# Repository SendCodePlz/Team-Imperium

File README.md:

<div align="center">

# Team Imperium — Battery Management System

**A hardware + software BMS for 3-series Li-ion packs: real-time fault detection, graded protection, and SOC/SOH estimation**

*Caterpillar Tech Challenge · IIT Madras*

</div>

---

## Overview

Team Imperium's BMS watches a battery pack's sensors in real time, works out whether something
dangerous is happening, and disconnects the pack before it fails. It has two parts:

- **Custom PCB.** A 2-layer board built around a TI **BQ77915** cell protector, with
  back-to-back **CSD17570Q5B** charge/discharge MOSFETs, an **INA226** current/power monitor on
  a 2 mΩ shunt, three thermistor inputs, and a socket for an **ESP32** dev board.
- **Firmware and toolchain.** ESP32 firmware on FreeRTOS that runs **14 physics-based fault
  detectors**, a severity → action-tier → contactor chain, and an **Unscented Kalman Filter**
  for State of Charge and State of Health. A Python toolchain replays labelled data through
  the same algorithm (Software-in-the-Loop) and scores it against ground truth.

### Highlights

| | |
|---|---|
| **Fault detection** | 14 detectors covering thermal, gas/pressure, mechanical impact, sensor loss, micro-short, voltage/thermal gradients, over/under-voltage, over-current and thermal-runaway precursors |
| **Graded response** | Each fault gets a 0–1 severity, which maps to one of 4 tiers: `NORMAL → INHIBIT_CHG → OPEN_ALL → LATCH_OPEN` |
| **State estimation** | Joint SOC/SOH UKF with a fitted OCV–SOC curve. SOC error is about 3%, down from about 13% with a generic NMC curve |
| **Verification** | The same algorithm runs in C++ on the ESP32 and in Python on a PC, scored against a 36,001-sample labelled dataset |
| **Telemetry** | Live terminal dashboard, matplotlib GUI, serial logs, and a WiFi UDP logger to CSV |

---

## Results

Software-in-the-Loop run over the full labelled dataset (`python monitor.py --sim --no-gui`):

| Metric | Value |
|---|---|
| **Precision** | **99.6 %** (TP 2862 / FP 12) |
| **Recall, all labelled faults** | 56 % |
| **Recall, excluding impedance growth** | 82 % |

| Fault class | Recall |
|---|---|
| Micro-short / abnormal self-heating | 95.0 % |
| Gas generation / pressure build-up | 82.0 % |
| Voltage sensor noise / loose lead | 73.6 % |
| Mechanical impact / obstacle hit | 70.2 % |
| Impedance growth / contact degradation | ≈ 0 % (see below) |

> **Why impedance growth is ≈0 %:** in this dataset it has no per-frame signature. It is a
> multi-cycle ageing effect, so the design tracks it through the UKF's SOH / power-fade trend
> instead of an instantaneous threshold. We kept the thresholds tied to the physics rather than
> tuning them to this dataset. Details are in
> [`software/fault_detection.md`](software/fault_detection.md).

---

## Hardware

<table>
<tr>
<td width="50%"></td>
<td width="50%"></td>
</tr>
<tr>
<td align="center"><b>Top side</b></td>
<td align="center"><b>Bottom side</b> (mirrored, as seen from below)</td>
</tr>
</table>

**Board:** 2-layer FR-4, about 129 × 118 mm, mostly hand-solderable SMD (0603 passives). Both
layers carry poured copper: GND on top and BATT+ on the bottom.

### Key components

| Ref | Part | Role |
|---|---|---|
| IC1 | TI **BQ77915** | 3–5S stackable cell protector: OV/UV, OC, short-circuit, OT/UT, passive balancing |
| Q1, Q2 (CFET / DFET) | TI **CSD17570Q5B** | Low-R<sub>DS(on)</sub> N-MOSFETs for the charge and discharge paths |
| U2 | TI **INA226** | High-side current / bus-voltage / power monitor over I²C |
| R11 | 2 mΩ WSK2512 shunt | Current sense |
| J9, J10 | 1×15 sockets | ESP32 dev board (3V3 side / VIN side) |
| J1–J4 | Pin pads | 12 V → 5 V buck module |
| TH1–TH3 | JST-PH 2-pin | Cell thermistors |
| J6 | JST-XH 4-pin | Cell balance / sense taps (3S) |
| J5, J12, J18 | 1×4 headers | Pressure sensor, OLED, IMU (I²C) |
| J11 | 5.08 mm screw terminal | Charging adapter input |
| TP1–TP4 | 5×10 mm solder pads | `BATT+`, `BATT−`, `PACK+`, `PACK−` |

Full bill of materials: [`hardware/bom/BMS_Imperium_BOM.csv`](hardware/bom/BMS_Imperium_BOM.csv).

### Opening the design

Open `hardware/BMS_Imperium.kicad_pro` in **KiCad 9.0 or later**. The custom footprints
(`BQ7761501`, `TRANS_CSD18512Q5B`) are embedded in the board file, so the PCB opens without the
`BMS.pretty` library. To regenerate Gerbers, use *File → Fabrication Outputs* in the PCB editor;
the job file is in `hardware/fabrication/`.

The PCB images above come from the board file via [`tools/render_pcb.py`](tools/render_pcb.py)
(details under [Regenerating the PCB renders](#regenerating-the-pcb-renders)).

---

## System architecture

```
                         ┌──────────────── PC (Python) ─────────────────┐
  labelled dataset ────► │ monitor.py ──► serial packets ──────────────►│──► ESP32 firmware
  (.xlsx / SIL .csv)     │   │                                          │      ├─ taskRX       (core 0)
                         │   ├─► detector_sim.py  (--sim, PC mirror)    │      ├─ taskProcess  (core 1)
                         │   ├─► dashboard.py / gui_plotter.py          │      │    UKF → 14 detectors
                         │   └─► csv_logger.py ◄── WiFi UDP ◄───────────│──────┤    → severity → tier
                         └──────────────────────────────────────────────┘      │    → MOSFETs / LEDs / buzzer
                                                                               └─ taskWiFiLog  (core 0)
```

**Decision chain, run once per frame:**

```
detectors ──► per-fault severity (0–1) ──► system severity = max ──► tier ──► contactors
                                                                      │
   0.00 ─── NORMAL ─── 0.30 ── INHIBIT_CHG ── 0.55 ── OPEN_ALL ── 0.80 ── LATCH_OPEN ── 1.00
            log + LED         open charge FET        open both FETs       open both + latch
```

The full design is documented in [`software/README.md`](software/README.md), including every
detector, the severity calibration, the run modes and the GPIO map.

---

## Repository structure

```
Team-Imperium/
├── README.md                       ← you are here
├── docs/
│   └── images/                     PCB renders used in this README
├── hardware/                       KiCad 9 project
│   ├── BMS_Imperium.kicad_pro
│   ├── BMS_Imperium.kicad_sch      schematic
│   ├── BMS_Imperium.kicad_pcb      board layout
│   ├── fp-lib-table
│   ├── bom/                        bill of materials (CSV)
│   ├── fabrication/                Gerber job file
│   └── reports/                    schematic → PCB update report
├── software/                       firmware + Python toolchain
│   ├── BMS_ESP32_Demo/             ESP32 Arduino firmware (FreeRTOS)
│   │   ├── BMS_ESP32_Demo.ino      tasks: RX, Process, WiFiLog
│   │   ├── config.h                all thresholds, pins, WiFi settings
│   │   ├── detectors.h             detectors + severity + hardware control
│   │   ├── types.h                 Frame / DetectorState, FaultID enum
│   │   ├── wifi_log.h              UDP payload builder
│   │   └── src/ukf_soh/            on-device SOC/SOH UKF
│   ├── monitor.py                  orchestrator / data player (entry point)
│   ├── detector_sim.py             Python mirror of detectors.h
│   ├── soc_ukf.py                  Python mirror of the UKF
│   ├── bms_state.py                shared state + fault catalogue
│   ├── dashboard.py                Rich terminal dashboard
│   ├── gui_plotter.py              live matplotlib GUI
│   ├── csv_logger.py               WiFi UDP → CSV receiver
│   ├── synthetic_NMC__1C_fault_EIS_dataset.xlsx
│   ├── requirements.txt
│   ├── README.md                   full technical reference
│   ├── fault_detection.md          physics-first detector design spec
│   └── PRESENTATION.md             presenter's guide and Q&A
└── tools/
    └── render_pcb.py               .kicad_pcb → PNG renderer
```

---

## Getting started

### 1. Python toolchain

Requires Python 3.10 or later.

```bash
cd software
```

```bash
pip install -r requirements.txt
```

```bash
python monitor.py
```

Running `monitor.py` with no arguments opens an interactive menu. You can also pick a mode
directly:

| Command | What it does |
|---|---|
| `python monitor.py --sim` | Runs the real detection algorithm on the PC and scores it |
| `python monitor.py --sim --no-gui --speed 1000` | Fast headless scoring with per-fault and per-detector breakdowns |
| `python monitor.py --dry-run` | Replays the dataset's labels (checks the UI only) |
| `python monitor.py --port COM3` | Streams data to the ESP32 over serial (on Linux `/dev/ttyUSB0`, on macOS `/dev/tty.usbserial-*`) |
| `python monitor.py --port COM3 --wifi` | Same, and also logs the board's WiFi telemetry to `wifi_log.csv` |

### 2. ESP32 firmware

1. Install the **ESP32 board package** in the Arduino IDE, plus the *Adafruit SSD1306* and
   *Adafruit GFX* libraries.
2. Open `software/BMS_ESP32_Demo/BMS_ESP32_Demo.ino`.
3. Edit `config.h`. For WiFi logging, set `WIFI_SSID`, `WIFI_PASS` and `LOG_SERVER_IP` (your
   PC's LAN IP).
4. Flash the board, then run `monitor.py --port <PORT>`.

> **Keep the copies in sync:** the thresholds exist in both `config.h` and `detector_sim.py`,
> and the `FaultID` order must match across `types.h`, `bms_state.py` and `detector_sim.py`.
> If you change one, change the others.

---

## Regenerating the PCB renders

```bash
pip install sexpdata matplotlib
```

```bash
python tools/render_pcb.py hardware/BMS_Imperium.kicad_pcb docs/images/pcb
```

This writes `pcb_front.png` and `pcb_back.png`. If you have KiCad 9 installed,
`kicad-cli pcb render` gives photorealistic 3D renders as an alternative.

---

## Documentation

| Document | Contents |
|---|---|
| [`software/README.md`](software/README.md) | Full technical reference: data pipeline, all detectors, severity system, run modes, sensors, GPIO map, tuning workflow |
| [`software/fault_detection.md`](software/fault_detection.md) | Physics-first detector design and the dual-mode RUL plan |
| [`software/PRESENTATION.md`](software/PRESENTATION.md) | Narrative walkthrough, demo script and anticipated Q&A |

---

<div align="center">

**Team Imperium · IIT Madras** — built for the Caterpillar Tech Challenge

</div>

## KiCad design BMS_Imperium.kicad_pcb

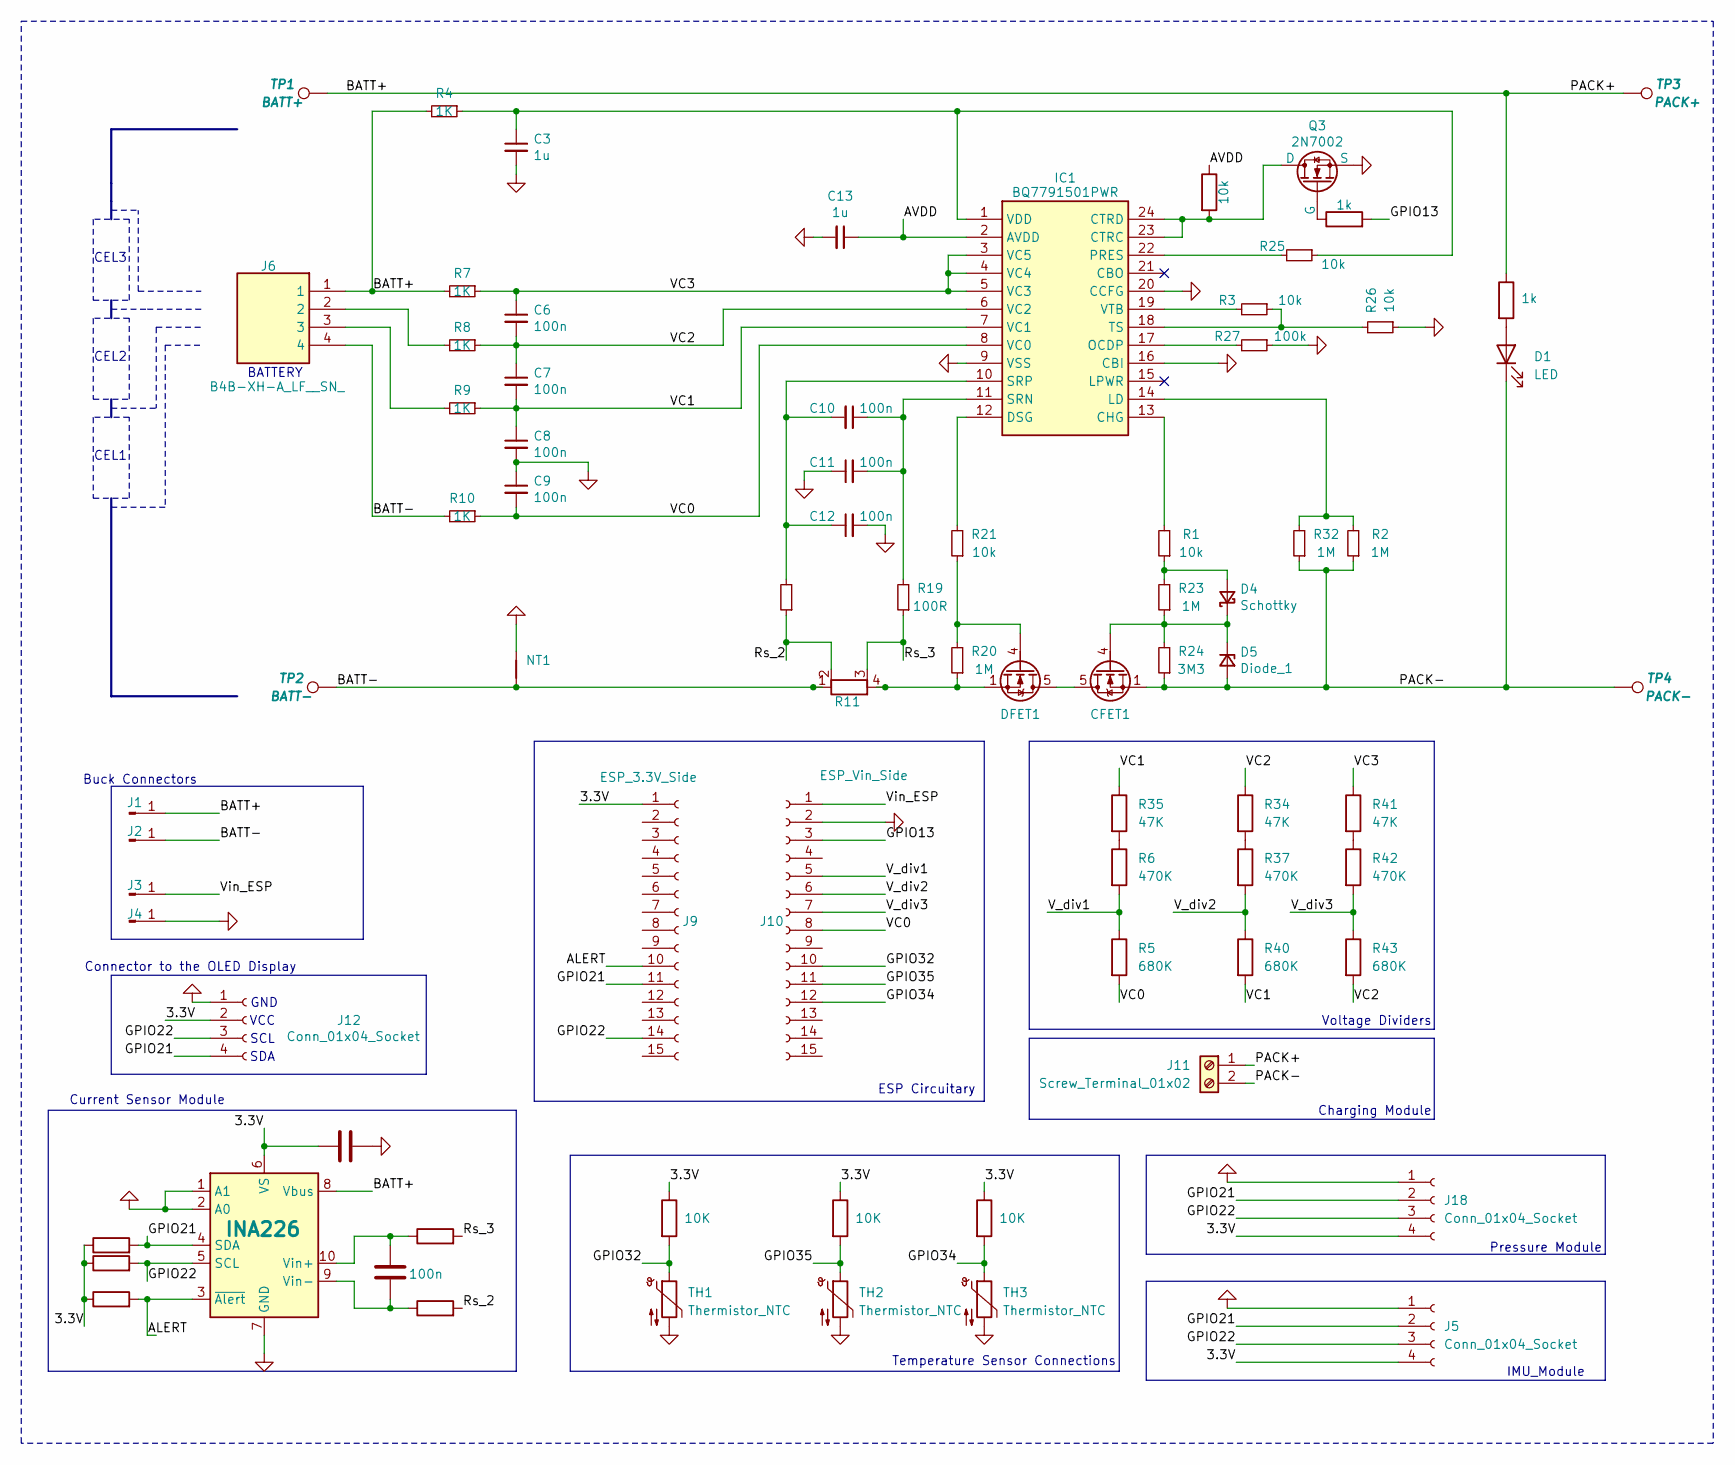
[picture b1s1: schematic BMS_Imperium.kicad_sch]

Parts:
C1: C; C_0603_1608Metric_Pad1.08x0.95mm_HandSolder
C2, C6, C7, C8, C9, C10, C11, C12: 100n; C_0603_1608Metric_Pad1.08x0.95mm_HandSolder
C3, C13: 1u; C_0603_1608Metric_Pad1.08x0.95mm_HandSolder
CFET1: CSD17570Q5B; VSON-8_3.3x3.3mm_P0.65mm_NexFET
D1: LED; LED_0805_2012Metric_Pad1.15x1.40mm_HandSolder
D4: Schottky; SOT-23_Handsoldering_1
D5: Diode_1; SOT-23_Handsoldering_1
DFET1: CSD17570Q5B; VSON-8_3.3x3.3mm_P0.65mm_NexFET
IC1: BQ7791501PWR; BQ7761501; Mouser Part Number 595-BQ7791501PWR
J1, J2, J3, J4: Conn_01x01_Pin; PinHeader_1x01_P2.54mm_Vertical
J5, J12, J18: Conn_01x04_Socket; PinSocket_1x04_P2.54mm_Vertical
J6: B4B-XH-A_LF__SN_; JST_XH_B4B-XH-A_1x04_P2.50mm_Vertical; Mouser Part Number 306-B4BXHALFSN
J9: ESP_3.3V_Side; PinSocket_1x15_P2.54mm_Vertical
J10: ESP_Vin_Side; PinSocket_1x15_P2.54mm_Vertical
J11: Screw_Terminal_01x02; TerminalBlock_Phoenix_MKDS-1,5-2-5.08_1x02_P5.08mm_Horizont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
NT1: NetTie_2; NetTie-2_SMD_Pad2.0mm
Q3: 2N7002; SOT-23_Handsoldering
R1, R3, R14, R21, R25, R26, R29: 10k; R_0603_1608Metric_Pad0.98x0.95mm_HandSolder
R2, R20, R23, R32: 1M; R_0603_1608Metric_Pad0.98x0.95mm_HandSolder
R4, R7, R8, R9, R10: 1K; R_0603_1608Metric_Pad0.98x0.95mm_HandSolder
R5, R40, R43: 680K; R_0603_1608Metric_Pad0.98x0.95mm_HandSolder
R6, R37, R42: 470K; R_0603_1608Metric_Pad0.98x0.95mm_HandSolder
R11: 2m; R_Shunt_Vishay_WSK2512_6332Metric_T2.21mm
R12, R16: 1k; R_0603_1608Metric_Pad0.98x0.95mm_HandSolder
R13, R28: 2.2k; R_0603_1608Metric_Pad0.98x0.95mm_HandSolder
R15, R19: 100R; R_0603_1608Metric_Pad0.98x0.95mm_HandSolder
R17, R18, R22: 10K; R_0603_1608Metric_Pad0.98x0.95mm_HandSolder
R24: 3M3; R_0603_1608Metric_Pad0.98x0.95mm_HandSolder
R27: 100k; R_0603_1608Metric_Pad0.98x0.95mm_HandSolder
R30, R31: 10; R_0603_1608Metric_Pad0.98x0.95mm_HandSolder
R34, R35, R41: 47K; R_0603_1608Metric_Pad0.98x0.95mm_HandSolder
TH1, TH2, TH3: Thermistor_NTC; JST_PH_B2B-PH-K_1x02_P2.00mm_Vertical
TP1: BATT+; SolderWirePad_1x01_SMD_5x10mm
TP2: BATT-; SolderWirePad_1x01_SMD_5x10mm
TP3: PACK+; SolderWirePad_1x01_SMD_5x10mm
TP4: PACK-; SolderWirePad_1x01_SMD_5x10mm
U2: INA226; VSSOP-10_3x3mm_P0.5mm

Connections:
/3.3V: C1.1, J5.4, J9.1, J12.2, J18.4, R13.1, R17.1, R18.1, R22.1, R28.1, R29.1, U2.6 (VS)
/<NO NET>: C7.2, C8.1, IC1.7 (VC1), R9.1, R35.1, R40.2
/ALERT: J9.10, R29.2, U2.3 (~Alert)
/AVDD: C13.1, IC1.2 (AVDD), R14.1
/BATT+: J1.1, J6.1, J11.1, R4.2, R7.2, R16.1, TP1.1, TP3.1, U2.8 (Vbus)
/BATT-: J2.1, J6.4, NT1.1, R10.2, R11.1, TP2.1
/GPIO13: J10.3, R12.2
/GPIO21: J5.2, J9.11, J12.4, J18.2, R13.2, U2.4 (SDA)
/GPIO22: J5.3, J9.14, J12.3, J18.3, R28.2, U2.5 (SCL)
/GPIO32: J10.10, R17.2, TH1.1
/GPIO34: J10.12, R22.2, TH3.1
/GPIO35: J10.11, R18.2, TH2.1
/PACK-: CFET1.1 (S), CFET1.2 (S), CFET1.3 (S), D1.1 (K), D5.2 (A), J11.2, R2.1, R24.1, R32.1, TP4.1
/Rs_2: R11.2, R15.1, R31.2
/Rs_3: R11.3, R19.1, R30.2
/VC0: C9.2, IC1.8 (VC0), J10.8, R5.2, R10.1
/VC2: C6.2, C7.1, IC1.6 (VC2), R8.1, R34.1, R43.2
/VC3: C6.1, IC1.3 (VC5), IC1.4 (VC4), IC1.5 (VC3), R7.1, R41.1
/V_div1: J10.5, R5.1, R6.2
/V_div2: J10.6, R37.2, R40.1
/V_div3: J10.7, R42.2, R43.1
/Vin_ESP: J3.1, J10.1
GND: C1.2, C3.2, C8.2, C9.1, C11.1, C12.2, C13.2, IC1.9 (VSS), IC1.16 (CBI), IC1.20 (CCFG), J4.1, J5.1, J10.2, J12.1, J18.1, NT1.2, Q3.2 (S), R26.1, R27.1, TH1.2, TH2.2, TH3.2, U2.1 (A1), U2.2 (A0), U2.7 (GND)
unnamed: CFET1.5 (D), DFET1.5 (D)
unnamed: CFET1.4 (G), D4.1 (K), D5.1 (K), R23.1, R24.2
unnamed: D1.2 (A), R16.2
unnamed: D4.2 (A), R1.1, R23.2
unnamed: DFET1.4 (G), R20.2, R21.1
unnamed: DFET1.1 (S), DFET1.2 (S), DFET1.3 (S), R11.4, R20.1
unnamed: IC1.13 (CHG), R1.2
unnamed: IC1.23 (CTRC), IC1.24 (CTRD), Q3.3 (D), R14.2
unnamed: IC1.12 (DSG), R21.2
unnamed: IC1.14 (LD), R2.2, R32.2
unnamed: IC1.17 (OCDP), R27.2
unnamed: IC1.22 (PRES), R25.2
unnamed: C10.1, C11.2, IC1.11 (SRN), R19.2
unnamed: C10.2, C12.1, IC1.10 (SRP), R15.2
unnamed: IC1.18 (TS), R3.1, R26.2
unnamed: C3.1, IC1.1 (VDD), R4.1, R25.1
unnamed: IC1.19 (VTB), R3.2
unnamed: J6.2, R8.2
unnamed: J6.3, R9.2
unnamed: Q3.1 (G), R12.1
unnamed: R34.2, R37.1
unnamed: R6.1, R35.2
unnamed: R41.2, R42.1
unnamed: C2.1, R30.1, U2.10 (Vin+)
unnamed: C2.2, R31.1, U2.9 (Vin-)

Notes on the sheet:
Temperature Sensor Connections
Buck Connectors
CEL2
BATTERY
Charging Module
SCL
CEL3
ESP Circuitary
GND
Voltage Dividers
Current Sensor Module
Pressure Module
IMU_Module
VCC
Connector to the OLED Display
SDA
CEL1

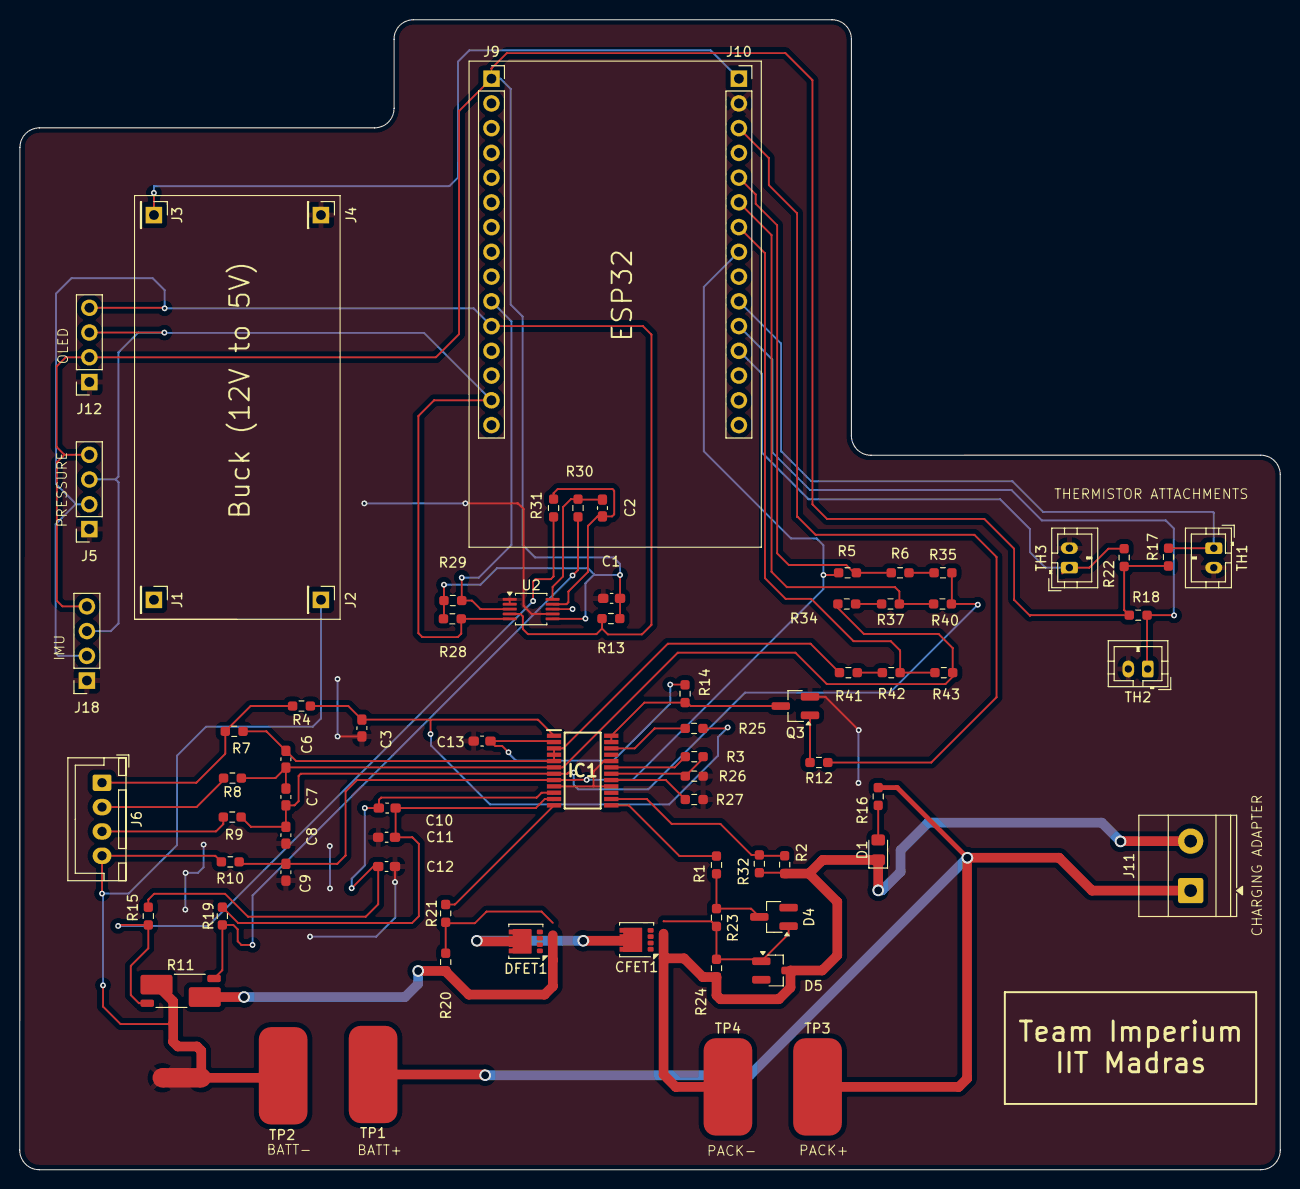
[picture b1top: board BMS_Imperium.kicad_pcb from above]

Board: 2 copper layers, 129.4 x 118.0 mm, 77 parts (0 on the bottom side), 48 nets.

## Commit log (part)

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2026-04-30 Initial commit (code only, no dataset)
2026-04-30 Organisation
2026-04-30 Gitignore
2026-05-02 OCV Model Check
2026-05-03 Incoorporating OCV with SOH
2026-05-07 Refining OCV Curve estimation
2026-05-07 Remove setup and run sections from README
    Removed setup and run instructions from README.
2026-06-18 More Changes look into final Submission
2026-06-25 Main Code
